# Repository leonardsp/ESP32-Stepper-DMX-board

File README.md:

# ESP32-Stepper-DMX-board

## DMX Channels

The current firmware implements the real motor + LED-dimmer DMX profile. There is no WLED DMX implementation in this build.

Combined fixture profile (LED dimmer default start address = 8):

1   - LED Pan
2   - LED Pan fine
3   - Ref Pan
4   - Ref Pan fine
5   - LED Pan Inv (0 stop / 1-127 CCW / 128 stop / 129-255 CW)
6   - Ref Pan Inv (0 stop / 1-127 CCW / 128 stop / 129-255 CW)
7   - Reset / Homing (0 no / 1-255 start)
8   - Dimmer 0 coarse
9   - Dimmer 0 fine
10  - Dimmer 1 coarse
11  - Dimmer 1 fine
12  - Dimmer 2 coarse
13  - Dimmer 2 fine
14  - Dimmer 3 coarse
15  - Dimmer 3 fine
16  - Dimmer 4 coarse
17  - Dimmer 4 fine
18  - Dimmer 5 coarse
19  - Dimmer 5 fine
20  - Dimmer 6 coarse
21  - Dimmer 6 fine
22  - Dimmer 7 coarse
23  - Dimmer 7 fine
24  - Strobe (0 off / 1-255 speed)
25-240 - RGB pixel data for 72 LEDs (3 channels per LED)

## Connector Pinout
1 - GND
2 - +24V
3 - DMX_B (xlr pin 2)
4 - DMX_A (xlr pin 3)

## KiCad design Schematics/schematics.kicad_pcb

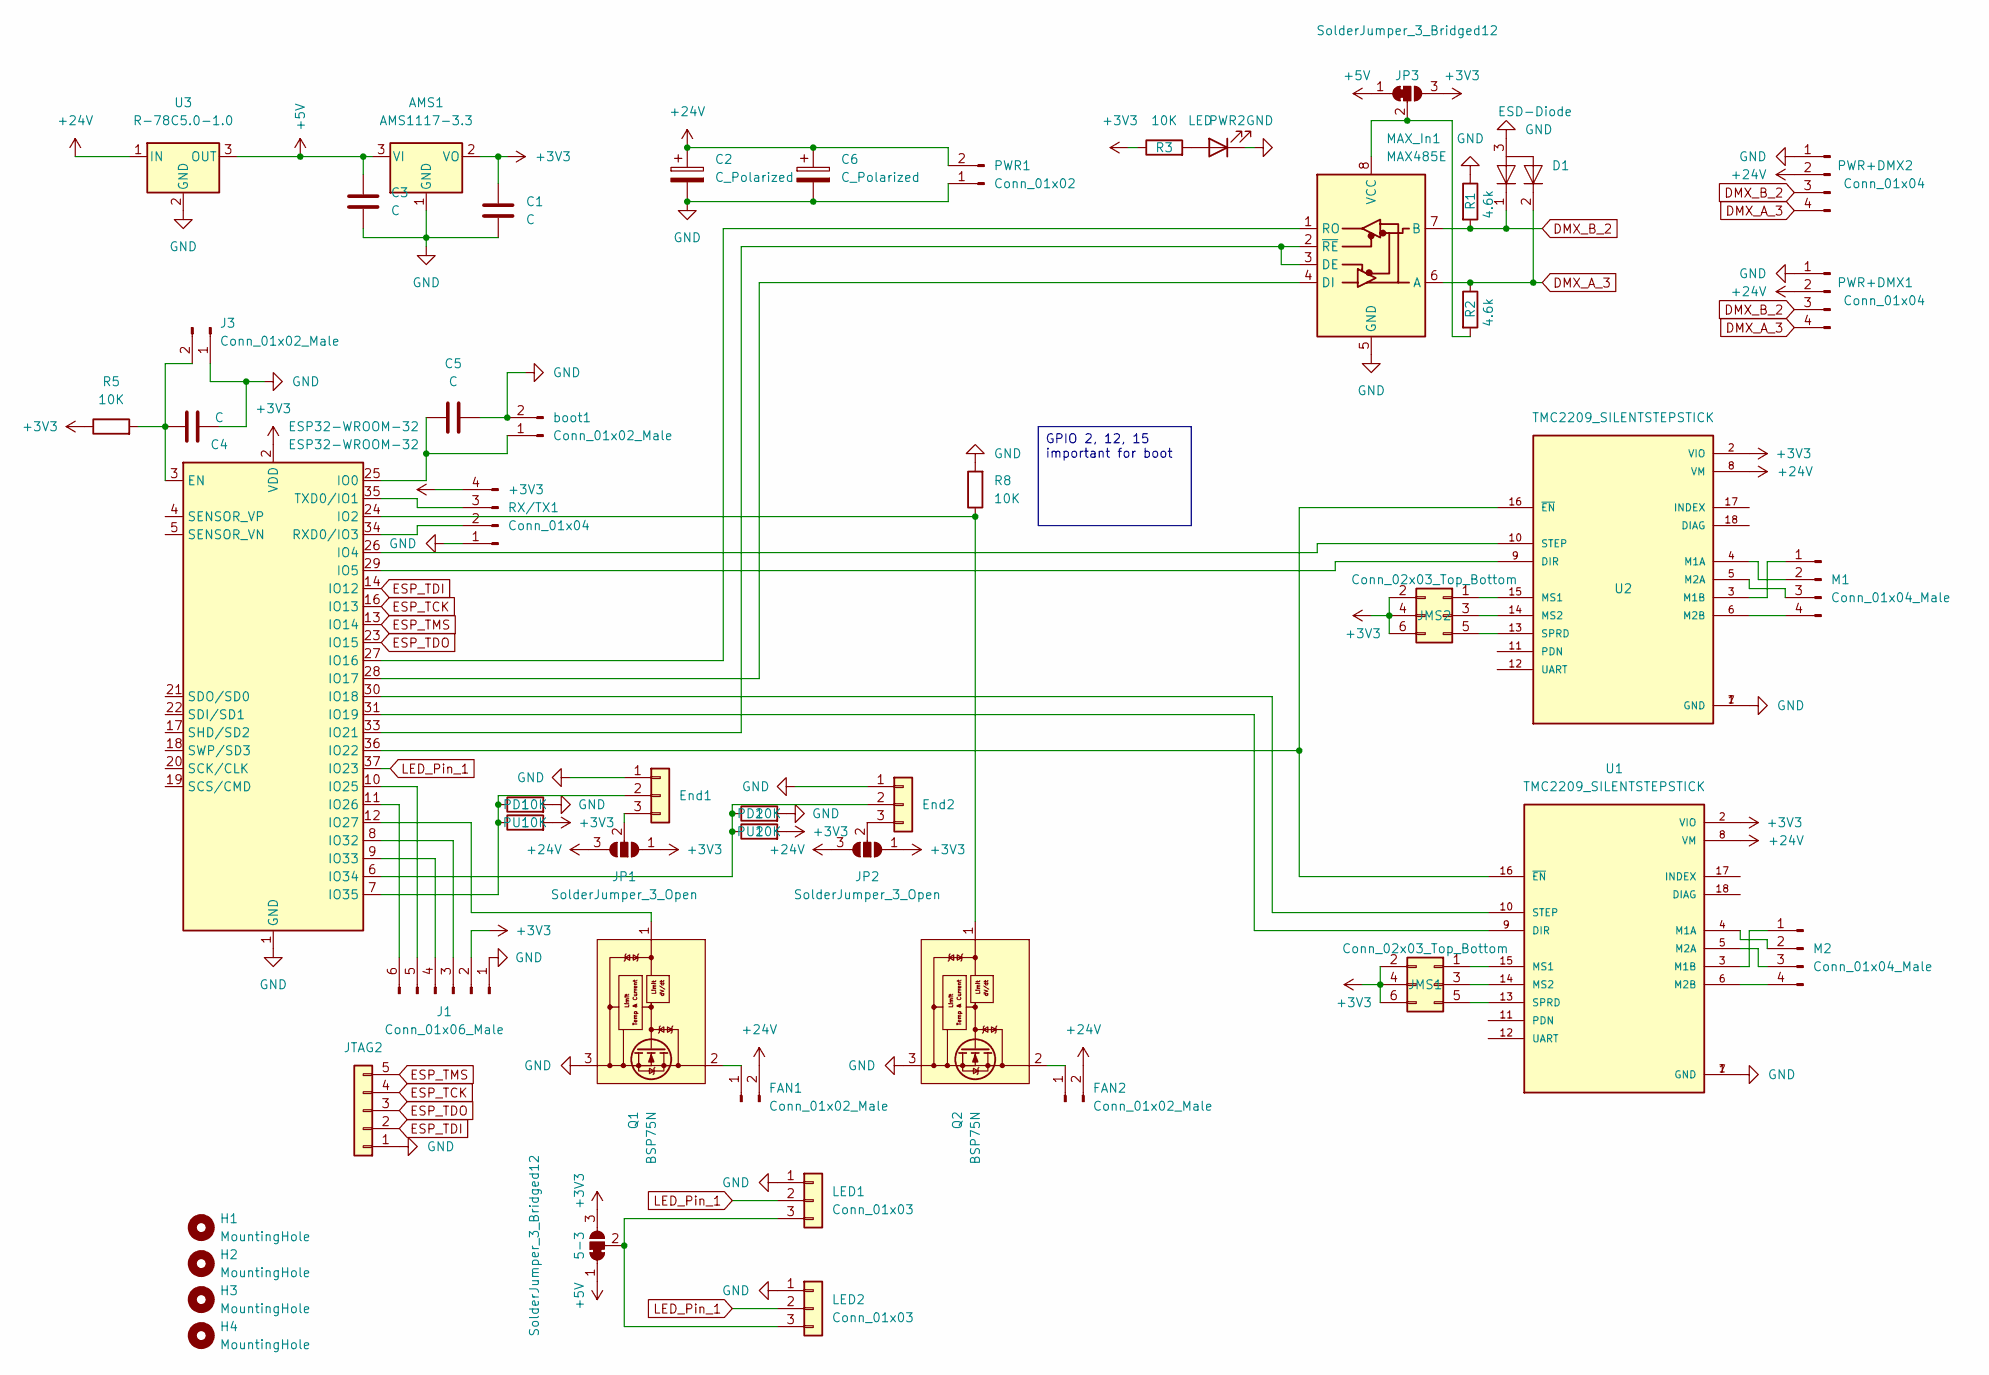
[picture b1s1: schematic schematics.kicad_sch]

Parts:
5-3: SolderJumper_3_Bridged12; SolderJumper-3_P1.3mm_Bridged12_Pad1.0x1.5mm
AMS1: AMS1117-3.3; SOT-223-3_TabPin2
C1: C; C_1210_3225Metric
C2, C6: C_Polarized; CP_Radial_D5.0mm_P2.00mm
C3: C; CP_Radial_D5.0mm_P2.50mm
C4, C5: C; C_1206_3216Metric
D1: ESD-Diode; SOT-23
ESP32-WROOM-32: ESP32-WROOM-32
End1, End2: Conn_01x03; FanPinHeader_1x03_P2.54mm_Vertical
FAN1, FAN2: Conn_01x02_Male; Molex_KK-254_AE-6410-02A_1x02_P2.54mm_Vertical
H1, H2, H3, H4: MountingHole; MountingHole_3.2mm_M3_DIN965
J1: Conn_01x06_Male; Molex_KK-254_AE-6410-06A_1x06_P2.54mm_Vertical
J2: JTAG2; PinHeader_1x05_P2.54mm_Vertical
J3: Conn_01x02_Male; PinHeader_1x02_P2.54mm_Vertical
JMS1, JMS2: Conn_02x03_Top_Bottom; PinHeader_2x03_P2.54mm_Vertical
JP1, JP2: SolderJumper_3_Open; SolderJumper-3_P1.3mm_Open_Pad1.0x1.5mm
JP3: SolderJumper_3_Bridged12; SolderJumper-3_P1.3mm_Bridged12_Pad1.0x1.5mm
LED1: Conn_01x03; FanPinHeader_1x03_P2.54mm_Vertical
LED2: Conn_01x03; TerminalBlock_bornier-3_P5.08mm
M1, M2: Conn_01x04_Male; FanPinHeader_1x04_P2.54mm_Vertical
MAX_In1: MAX485E; SSOP-8_3.9x5.05mm_P1.27mm
PD1, PD2: 10K; R_1206_3216Metric
PU1, PU2: 10K; R_1206_3216Metric
PWR1: Conn_01x02; Molex_KK-254_AE-6410-02A_1x02_P2.54mm_Vertical
PWR2: LED; LED_D3.0mm
PWR+DMX1, PWR+DMX2: Conn_01x04; Molex_KK-254_AE-6410-04A_1x04_P2.54mm_Vertical
Q1, Q2: BSP75N; SOT-223
R1, R2: 4.6k; R_1206_3216Metric
R3, R5, R8: 10K; R_1206_3216Metric
RX/TX1: Conn_01x04; Molex_KK-254_AE-6410-04A_1x04_P2.54mm_Vertical
U1, U2: TMC2209_SILENTSTEPSTICK; MODULE_TMC2209_SILENTSTEPSTICK
U3: R-78C5.0-1.0; Converter_DCDC_RECOM_R-78E-0.5_THT
boot1: Conn_01x02_Male; PinHeader_1x02_P2.54mm_Vertical

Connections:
+3V3: 5-3.3 (B), AMS1.2 (VO), C1.2, ESP32-WROOM-32.2 (VDD), J1.2, JMS1.2, JMS1.4, JMS1.6, JMS2.2, JMS2.4, JMS2.6, JP1.1 (A), JP2.1 (A), JP3.3 (B), PU1.2, PU2.2, R3.1, R5.1, RX/TX1.4, U1.2 (VIO), U2.2 (VIO)
+5V: 5-3.1 (A), AMS1.3 (VI), C3.1, JP3.1 (A), U3.3 (OUT)
+24V: C2.1, C6.1, FAN1.2, FAN2.2, JP1.3 (B), JP2.3 (B), PWR1.2, PWR+DMX1.2, PWR+DMX2.2, U1.8 (VM), U2.8 (VM), U3.1 (IN)
DMX_A_3: D1.2, MAX_In1.6 (A), PWR+DMX1.4, PWR+DMX2.4, R2.1
DMX_B_2: D1.1, MAX_In1.7 (B), PWR+DMX1.3, PWR+DMX2.3, R1.2
ESP_TCK: ESP32-WROOM-32.16 (IO13), J2.4
ESP_TDI: ESP32-WROOM-32.14 (IO12), J2.2
ESP_TDO: ESP32-WROOM-32.23 (IO15), J2.3
ESP_TMS: ESP32-WROOM-32.13 (IO14), J2.5
GND: AMS1.1 (GND), C1.1, C2.2, C3.2, C4.2, C5.2, C6.2, D1.3, ESP32-WROOM-32.1 (GND), ESP32-WROOM-32.15 (GND), ESP32-WROOM-32.38 (GND), ESP32-WROOM-32.39 (GND), End1.1, End2.1, J1.1, J2.1, J3.1, LED1.1, LED2.1, MAX_In1.5 (GND), PD1.2, PD2.2, PWR1.1, PWR2.1 (K), PWR+DMX1.1, PWR+DMX2.1, Q1.3 (S), Q1.4 (S), Q2.3 (S), Q2.4 (S), R1.1, R8.2, RX/TX1.1, U1.1 (GND), U1.7 (GND), U2.1 (GND), U2.7 (GND), U3.2 (GND), boot1.2
LED_Pin_1: ESP32-WROOM-32.37 (IO23), LED1.2, LED2.2
unnamed: 5-3.2 (C), LED1.3, LED2.3
unnamed: C4.1, ESP32-WROOM-32.3 (EN), J3.2, R5.2
unnamed: C5.1, ESP32-WROOM-32.25 (IO0), boot1.1
unnamed: ESP32-WROOM-32.6 (IO34), End2.2, PD2.1, PU2.1
unnamed: ESP32-WROOM-32.7 (IO35), End1.2, PD1.1, PU1.1
unnamed: ESP32-WROOM-32.8 (IO32), J1.3
unnamed: ESP32-WROOM-32.9 (IO33), J1.4
unnamed: ESP32-WROOM-32.10 (IO25), J1.5
unnamed: ESP32-WROOM-32.11 (IO26), J1.6
unnamed: ESP32-WROOM-32.12 (IO27), Q1.1 (G)
unnamed: ESP32-WROOM-32.24 (IO2), Q2.1 (G), R8.1
unnamed: ESP32-WROOM-32.26 (IO4), U2.10 (STEP)
unnamed: ESP32-WROOM-32.27 (IO16), MAX_In1.1 (RO)
unnamed: ESP32-WROOM-32.28 (IO17), MAX_In1.4 (DI)
unnamed: ESP32-WROOM-32.29 (IO5), U2.9 (DIR)
unnamed: ESP32-WROOM-32.30 (IO18), U1.10 (STEP)
unnamed: ESP32-WROOM-32.31 (IO19), U1.9 (DIR)
unnamed: ESP32-WROOM-32.33 (IO21), MAX_In1.2 (~RE), MAX_In1.3 (DE)
unnamed: ESP32-WROOM-32.34 (RXD0/IO3), RX/TX1.2
unnamed: ESP32-WROOM-32.35 (TXD0/IO1), RX/TX1.3
unnamed: ESP32-WROOM-32.36 (IO22), U1.16 (~EN), U2.16 (~EN)
unnamed: End1.3, JP1.2 (C)
unnamed: End2.3, JP2.2 (C)
unnamed: FAN1.1, Q1.2 (D)
unnamed: FAN2.1, Q2.2 (D)
unnamed: JMS1.1, U1.15 (MS1)
unnamed: JMS1.3, U1.14 (MS2)
unnamed: JMS1.5, U1.13 (SPRD)
unnamed: JMS2.1, U2.15 (MS1)
unnamed: JMS2.3, U2.14 (MS2)
unnamed: JMS2.5, U2.13 (SPRD)
unnamed: JP3.2 (C), MAX_In1.8 (VCC), R2.2
unnamed: M1.1, U2.3 (M1B)
unnamed: M1.2, U2.4 (M1A)
unnamed: M1.3, U2.5 (M2A)
unnamed: M1.4, U2.6 (M2B)
unnamed: M2.1, U1.3 (M1B)
unnamed: M2.2, U1.4 (M1A)
unnamed: M2.3, U1.5 (M2A)
unnamed: M2.4, U1.6 (M2B)
unnamed: PWR2.2 (A), R3.2

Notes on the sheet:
GPIO 2, 12, 15 important for boot

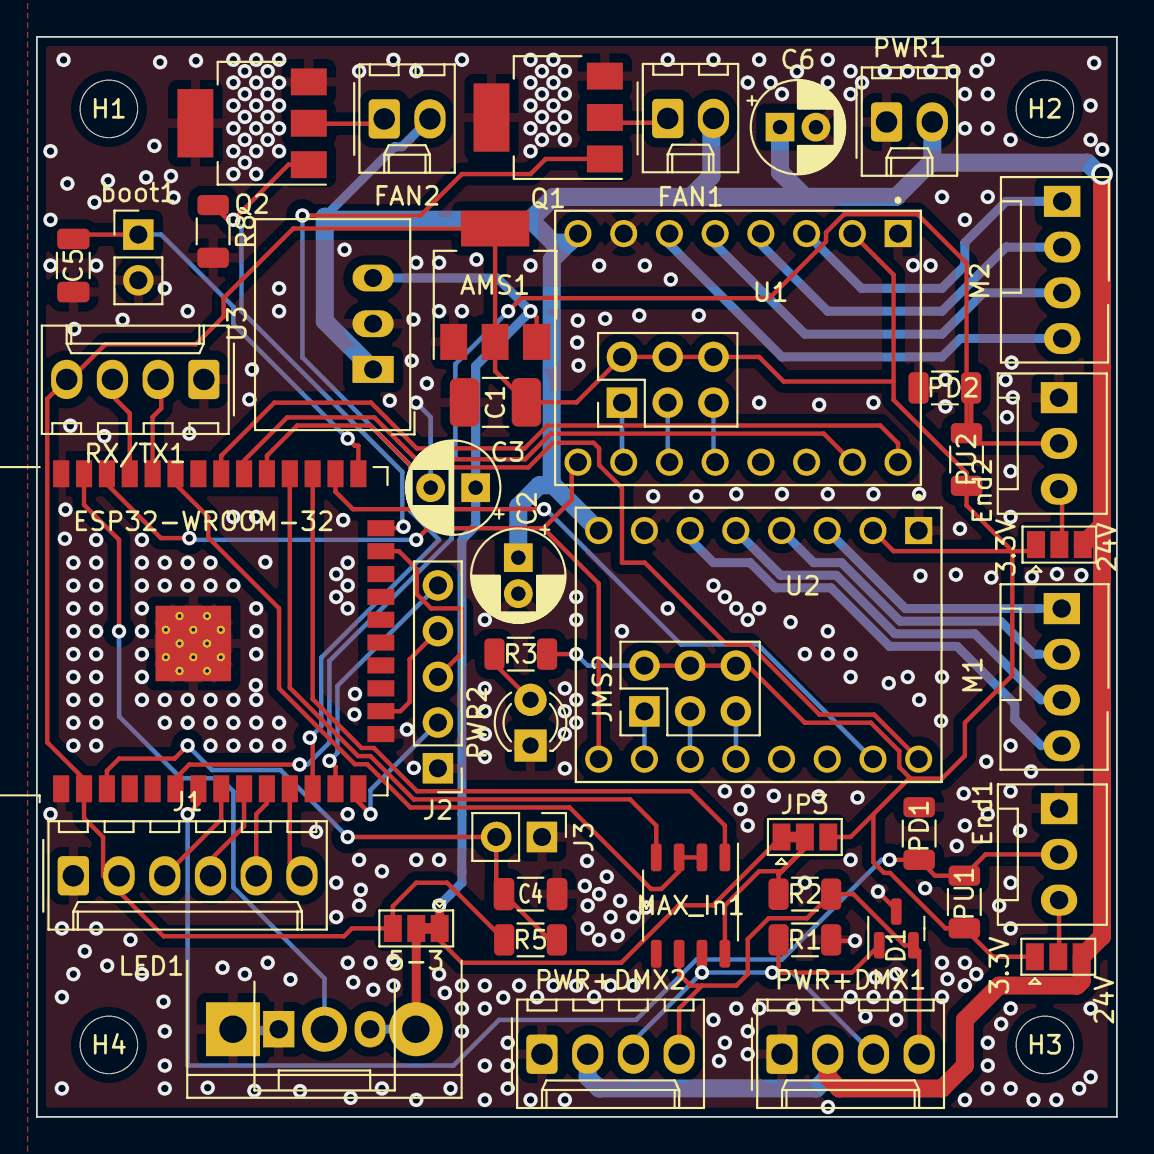
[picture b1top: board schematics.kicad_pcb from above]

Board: 2 copper layers, 60.0 x 60.0 mm, 51 parts (0 on the bottom side), 52 nets.

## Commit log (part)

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2024-11-28 first
2025-01-16 version 1
2026-01-07 Expand TODO.md with new sections
    Added sections for Mechanics, Electronics, and Software in TODO.md.
2026-01-07 Update TODO list with additional test items
2026-01-17 Update README with DMX channel details
    Added detailed DMX channel information for the ESP32 Stepper DMX board.
2026-01-17 Format README.md for better readability
2026-01-18 Update DMX channels in README
    Added new DMX channels for PanLEDinv and PanRefinv.
2026-01-18 Revise DMX channel details in README.md
    Updated DMX channel descriptions for clarity and added Strope channel.
2026-01-18 Fix formatting of README.md header and content
2026-01-18 Update README with DMX channels and pinout
2026-01-18 test dmx receive and led dimmer functionality
